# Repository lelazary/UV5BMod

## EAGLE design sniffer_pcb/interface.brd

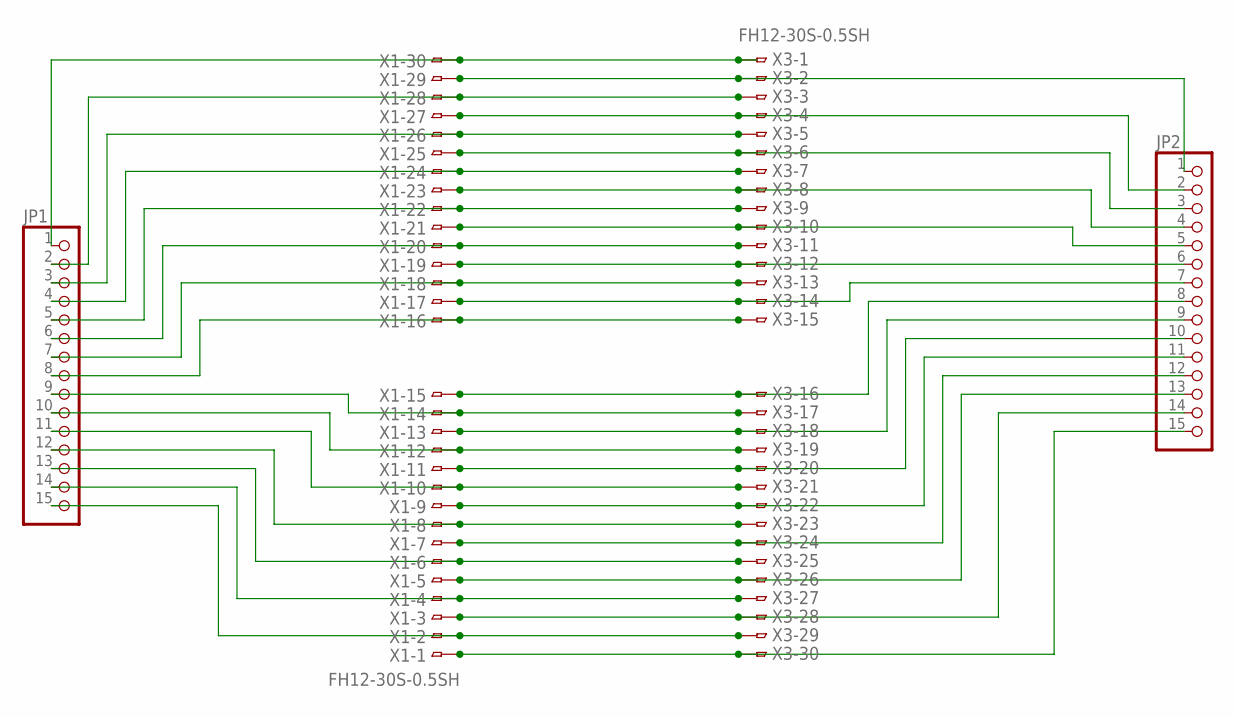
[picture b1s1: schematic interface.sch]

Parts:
JP1, JP2: PINHD-1X15; 1X15
X1, X3: FH12-30S-0.5SH

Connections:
unnamed: JP1.1, X1.30, X3.1
unnamed: JP2.1, X1.29, X3.2
unnamed: JP2.2, X1.27, X3.4
unnamed: JP1.3, X1.26, X3.5
unnamed: JP2.3, X1.25, X3.6
unnamed: JP1.4, X1.24, X3.7
unnamed: JP2.10, X1.11, X3.20
unnamed: JP2.11, X1.9, X3.22
unnamed: JP2.12, X1.7, X3.24
unnamed: JP2.4, X1.23, X3.8
unnamed: JP1.5, X1.22, X3.9
unnamed: JP2.5, X1.21, X3.10
unnamed: JP1.6, X1.20, X3.11
unnamed: JP2.6, X1.19, X3.12
unnamed: JP1.7, X1.18, X3.13
unnamed: JP2.7, X1.17, X3.14
unnamed: JP1.8, X1.16, X3.15
unnamed: JP2.8, X1.15, X3.16
unnamed: JP1.9, X1.14, X3.17
unnamed: JP1.2, X1.28, X3.3
unnamed: JP1.11, X1.10, X3.21
unnamed: JP1.12, X1.8, X3.23
unnamed: JP1.13, X1.6, X3.25
unnamed: JP2.13, X1.5, X3.26
unnamed: JP1.14, X1.4, X3.27
unnamed: JP1.15, X1.2, X3.29
unnamed: JP2.15, X1.1, X3.30
unnamed: JP1.10, X1.12, X3.19
unnamed: JP2.14, X1.3, X3.28
unnamed: JP2.9, X1.13, X3.18

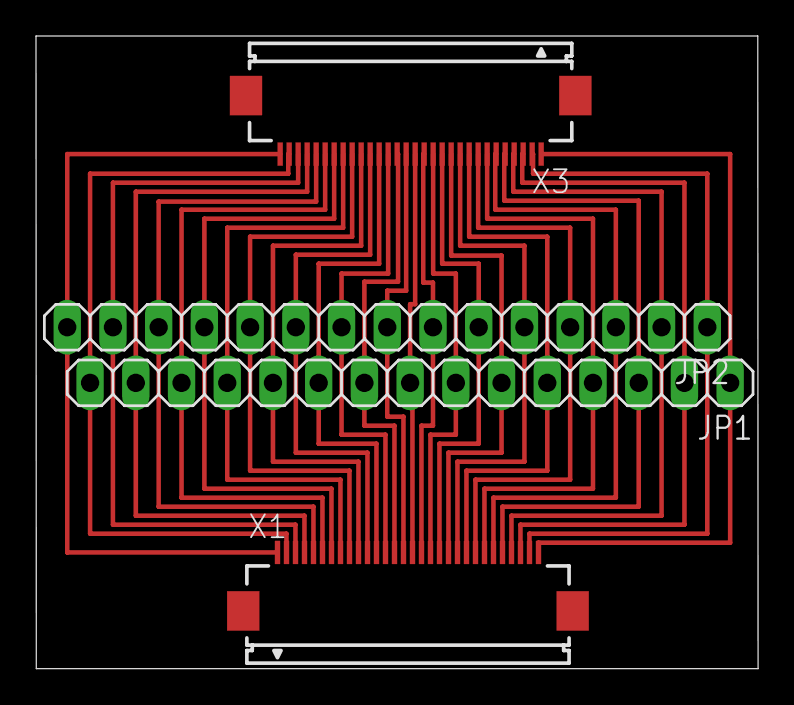
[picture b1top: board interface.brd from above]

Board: 2 copper layers, 40.1 x 35.1 mm, 4 parts (0 on the bottom side), 30 nets.

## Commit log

2013-12-01 Initial sniffer
2013-12-01 Added a scan of the original PCB for dimensions Move interface to its own directory
2013-12-01 Moved interface to its own directory
2013-12-01 inferface into its own directory
2014-06-05 Starting the firmware on the uvB5 with a teensy
2014-06-05 comm with RDA chip works
2014-06-06 Protocols captured with Agilent 54622D
2014-06-07 Added the 440 data
2014-06-07 Added more 440
2014-06-08 Figured out all the pins
2014-06-09 Fixed name
2014-06-09 Adding protocol values into readme
2014-06-09 Finished adding all the protocol data
